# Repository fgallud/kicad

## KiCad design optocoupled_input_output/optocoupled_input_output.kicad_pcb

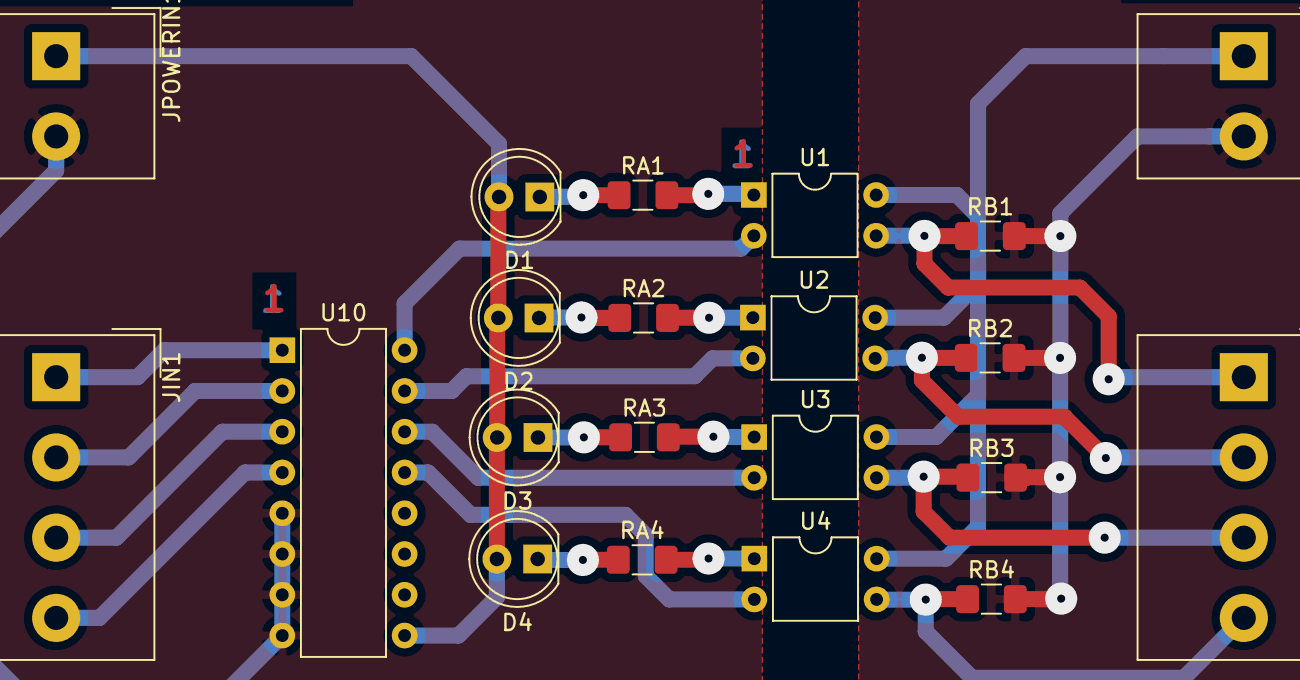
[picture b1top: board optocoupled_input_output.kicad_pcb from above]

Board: 2 copper layers, 21 parts (0 on the bottom side), 24 nets.

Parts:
D1, D2, D3, D4: LED; LED_D5.0mm
JIN1: Conn_01x04; Altech_AK300_1x04_P5.00mm_45-Degree
JOUT1: Conn_01x04; Altech_AK300_1x04_P5.00mm_45-Degree
JPOWERIN1: Conn_01x02; Altech_AK300_1x02_P5.00mm_45-Degree
JPOWEROUT1: Conn_01x02; Altech_AK300_1x02_P5.00mm_45-Degree
RA1, RA2, RA3, RA4: 2K2; R_1206_3216Metric_Pad1.42x1.75mm_HandSolder
RB1, RB2, RB3, RB4: 2K2; R_1206_3216Metric_Pad1.42x1.75mm_HandSolder
U1, U2, U3, U4: PC817; DIP-4_W7.62mm
U10: ULN2003; DIP-16_W7.62mm

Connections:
+3V3: JPOWEROUT1.1, U1.4, U2.4, U3.4, U4.4
+24V: D1.2, D2.2, D3.2, D4.2, JPOWERIN1.1, U10.9
GND: JPOWERIN1.2, U10.5, U10.6, U10.7, U10.8
GNDD: JPOWEROUT1.2, RB1.2, RB2.2, RB3.2, RB4.2
unnamed: D1.1, RA1.1
unnamed: D2.1, RA2.1
unnamed: D3.1, RA3.1
unnamed: D4.1, RA4.1
unnamed: JIN1.1, U10.1
unnamed: JIN1.2, U10.2
unnamed: JIN1.3, U10.3
unnamed: JIN1.4, U10.4
unnamed: JOUT1.1, RB1.1, U1.3
unnamed: JOUT1.2, RB2.1, U2.3
unnamed: JOUT1.3, RB3.1, U3.3
unnamed: JOUT1.4, RB4.1, U4.3
unnamed: RA1.2, U1.1
unnamed: RA2.2, U2.1
unnamed: RA3.2, U3.1
unnamed: RA4.2, U4.1
unnamed: U1.2, U10.16
unnamed: U4.2, U10.13
unnamed: U3.2, U10.14
unnamed: U2.2, U10.15

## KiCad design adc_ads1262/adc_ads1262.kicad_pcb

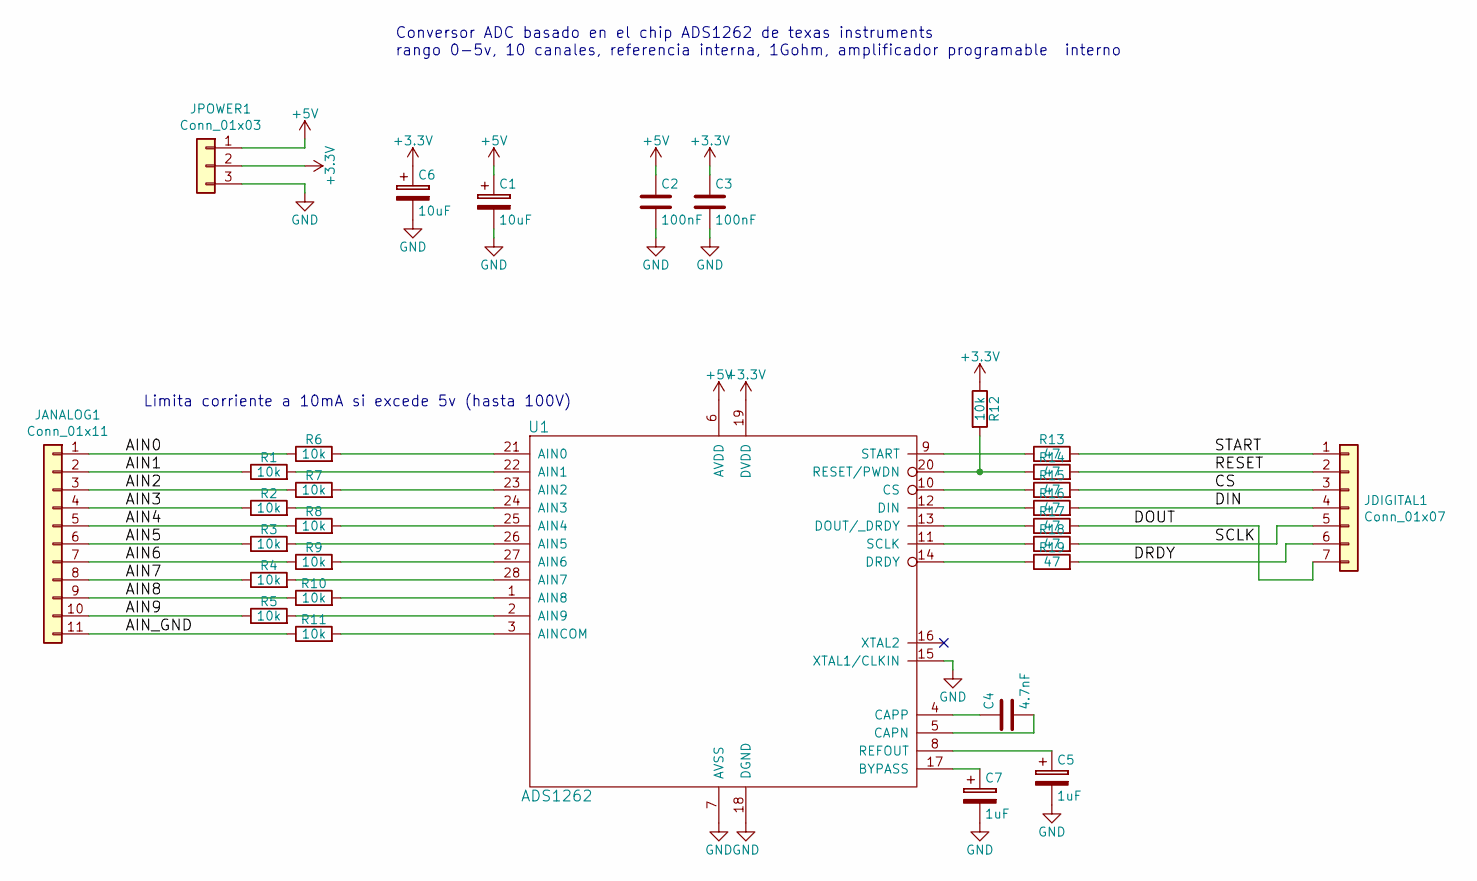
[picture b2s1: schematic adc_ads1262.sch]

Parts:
C1, C6: 10uF; CP_EIA-6032-28_Kemet-C_Pad2.25x2.35mm_HandSolder
C2, C3: 100nF; C_0805_2012Metric_Pad1.15x1.40mm_HandSolder
C4: 4.7nF; C_0805_2012Metric_Pad1.15x1.40mm_HandSolder
C5, C7: 1uF; CP_EIA-6032-28_Kemet-C_Pad2.25x2.35mm_HandSolder
JANALOG1: Conn_01x11; Altech_AK300_1x11_P5.00mm_45-Degree
JDIGITAL1: Conn_01x07; Altech_AK300_1x07_P5.00mm_45-Degree
JPOWER1: Conn_01x03; Altech_AK300_1x03_P5.00mm_45-Degree
R1, R2, R3, R4, R5, R6, R7, R8, R9, R10, R11, R12: 10k; R_0805_2012Metric_Pad1.15x1.40mm_HandSolder
R13, R14, R15, R16, R17, R18, R19: 47; R_0805_2012Metric_Pad1.15x1.40mm_HandSolder
U1: ADS1262; TSSOP-28_4.4x9.7mm_P0.65mm

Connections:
+3V3: C3.1, C6.1, JPOWER1.2, R12.1, U1.19 (DVDD)
+5V: C1.1, C2.1, JPOWER1.1, U1.6 (AVDD)
/AIN0: JANALOG1.1, R6.1
/AIN1: JANALOG1.2, R1.1
/AIN2: JANALOG1.3, R7.1
/AIN3: JANALOG1.4, R2.1
/AIN4: JANALOG1.5, R8.1
/AIN5: JANALOG1.6, R3.1
/AIN6: JANALOG1.7, R9.1
/AIN7: JANALOG1.8, R4.1
/AIN8: JANALOG1.9, R10.1
/AIN9: JANALOG1.10, R5.1
/AIN_GND: JANALOG1.11, R11.1
/CS: JDIGITAL1.3, R15.2
/DIN: JDIGITAL1.4, R16.2
/DOUT: JDIGITAL1.7, R17.2
/DRDY: JDIGITAL1.6, R19.2
/RESET: JDIGITAL1.2, R14.2
/SCLK: JDIGITAL1.5, R18.2
/START: JDIGITAL1.1, R13.2
GND: C1.2, C2.2, C3.2, C5.2, C6.2, C7.2, JPOWER1.3, U1.7 (AVSS), U1.15 (XTAL1/CLKIN), U1.18 (DGND)
unnamed: C4.1, U1.4 (CAPP)
unnamed: C4.2, U1.5 (CAPN)
unnamed: C5.1, U1.8 (REFOUT)
unnamed: C7.1, U1.17 (BYPASS)
unnamed: R1.2, U1.22 (AIN1)
unnamed: R2.2, U1.24 (AIN3)
unnamed: R3.2, U1.26 (AIN5)
unnamed: R4.2, U1.28 (AIN7)
unnamed: R5.2, U1.2 (AIN9)
unnamed: R6.2, U1.21 (AIN0)
unnamed: R7.2, U1.23 (AIN2)
unnamed: R8.2, U1.25 (AIN4)
unnamed: R9.2, U1.27 (AIN6)
unnamed: R10.2, U1.1 (AIN8)
unnamed: R11.2, U1.3 (AINCOM)
unnamed: R12.2, R14.1, U1.20 (RESET/PWDN)
unnamed: R13.1, U1.9 (START)
unnamed: R15.1, U1.10 (CS)
unnamed: R16.1, U1.12 (DIN)
unnamed: R17.1, U1.13 (DOUT/_DRDY)
unnamed: R18.1, U1.11 (SCLK)
unnamed: R19.1, U1.14 (DRDY)

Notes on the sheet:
Conversor ADC basado en el chip ADS1262 de texas instruments rango 0-5v, 10 canales, referencia interna, 1Gohm, amplificador programable interno
Limita corriente a 10mA si excede 5v (hasta 100V)

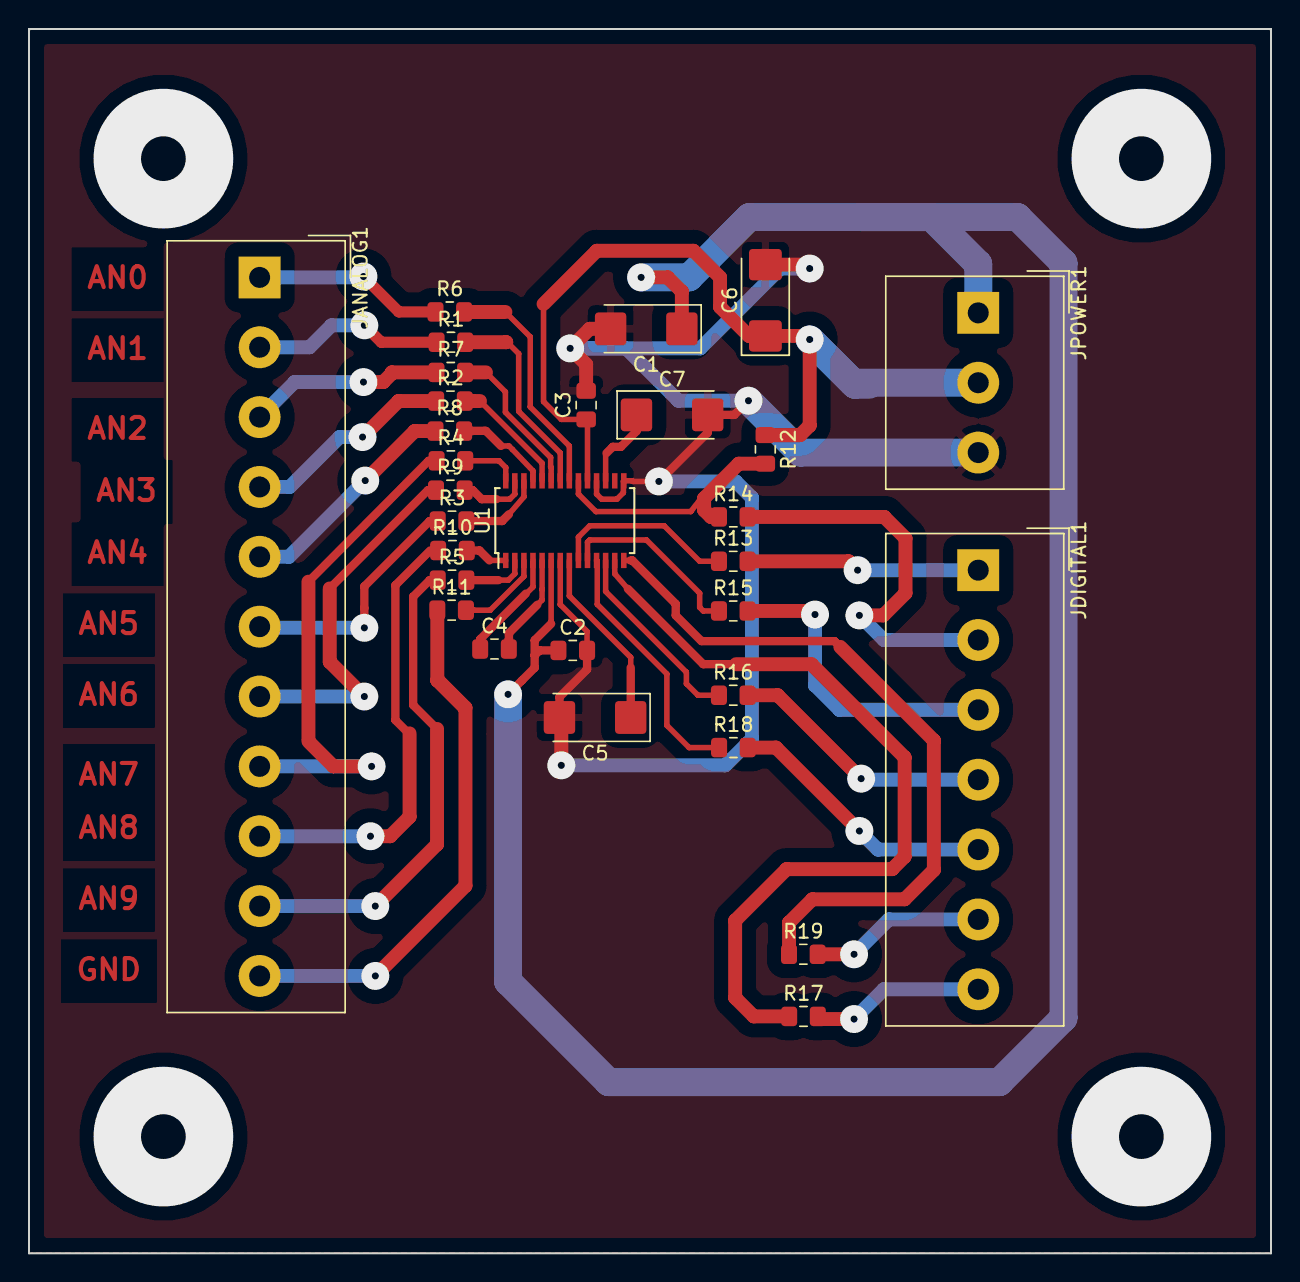
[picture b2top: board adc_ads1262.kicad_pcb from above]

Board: 2 copper layers, 88.9 x 87.6 mm, 30 parts (0 on the bottom side), 43 nets.

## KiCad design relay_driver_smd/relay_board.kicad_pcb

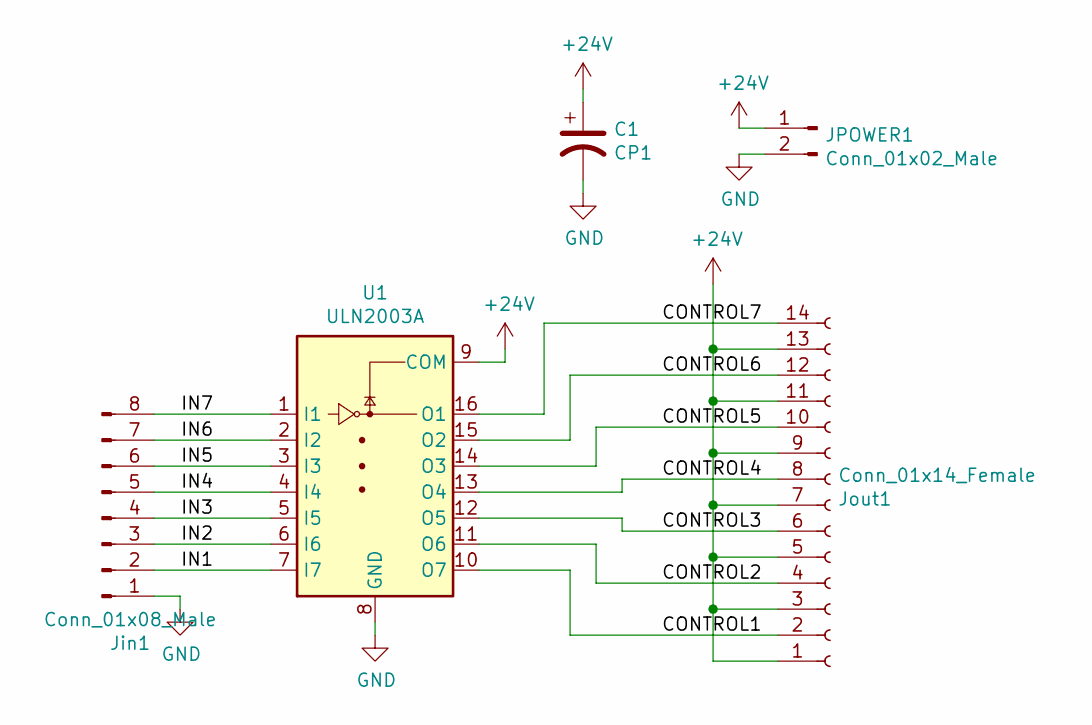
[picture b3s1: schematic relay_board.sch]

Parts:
C1: CP1; CP_EIA-7361-438_AVX-U_Pad2.18x3.30mm_HandSolder
JPOWER1: Conn_01x02_Male; Altech_AK300_1x02_P5.00mm_45-Degree
Jin1: Conn_01x08_Male; Altech_AK300_1x08_P5.00mm_45-Degree
Jout1: Conn_01x14_Female; Altech_AK300_1x14_P5.00mm_45-Degree
U1: ULN2003A; SOIC-16_4.55x10.3mm_P1.27mm

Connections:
+24V: C1.1, JPOWER1.1, Jout1.1, Jout1.3, Jout1.5, Jout1.7, Jout1.9, Jout1.11, Jout1.13, U1.9 (COM)
/CONTROL1: Jout1.2, U1.10 (O7)
/CONTROL2: Jout1.4, U1.11 (O6)
/CONTROL3: Jout1.6, U1.12 (O5)
/CONTROL4: Jout1.8, U1.13 (O4)
/CONTROL5: Jout1.10, U1.14 (O3)
/CONTROL6: Jout1.12, U1.15 (O2)
/CONTROL7: Jout1.14, U1.16 (O1)
/IN1: Jin1.2, U1.7 (I7)
/IN2: Jin1.3, U1.6 (I6)
/IN3: Jin1.4, U1.5 (I5)
/IN4: Jin1.5, U1.4 (I4)
/IN5: Jin1.6, U1.3 (I3)
/IN6: Jin1.7, U1.2 (I2)
/IN7: Jin1.8, U1.1 (I1)
GND: C1.2, JPOWER1.2, Jin1.1, U1.8 (GND)

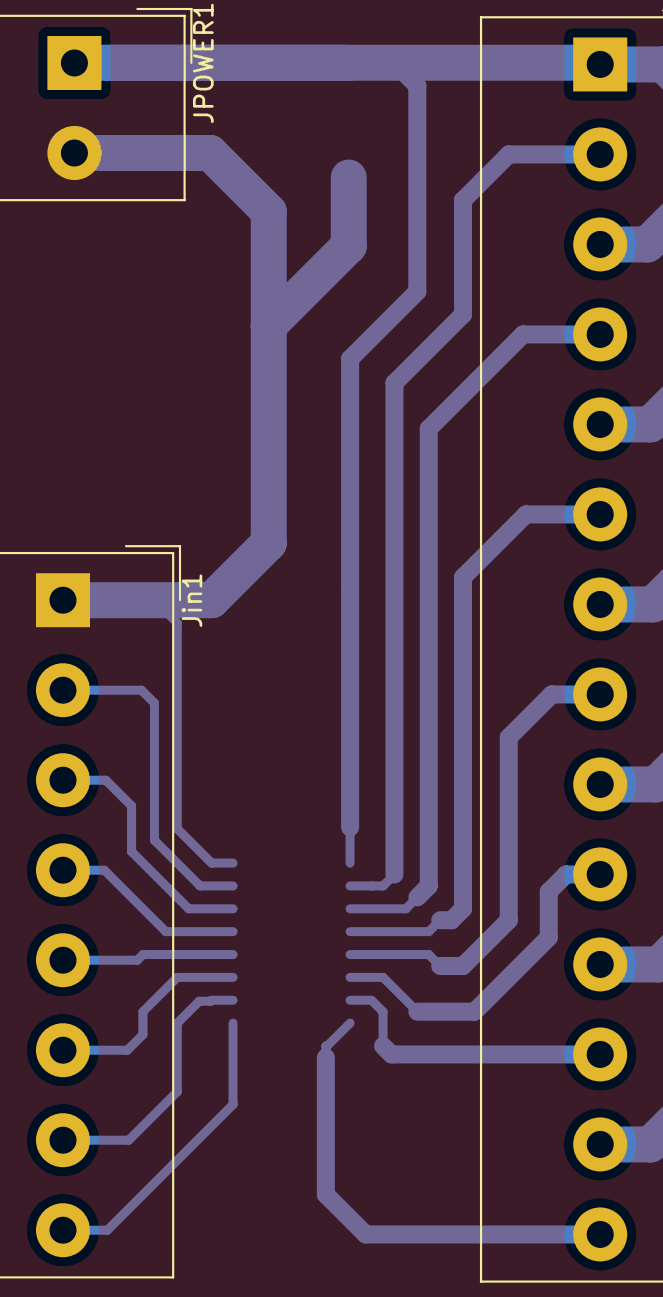
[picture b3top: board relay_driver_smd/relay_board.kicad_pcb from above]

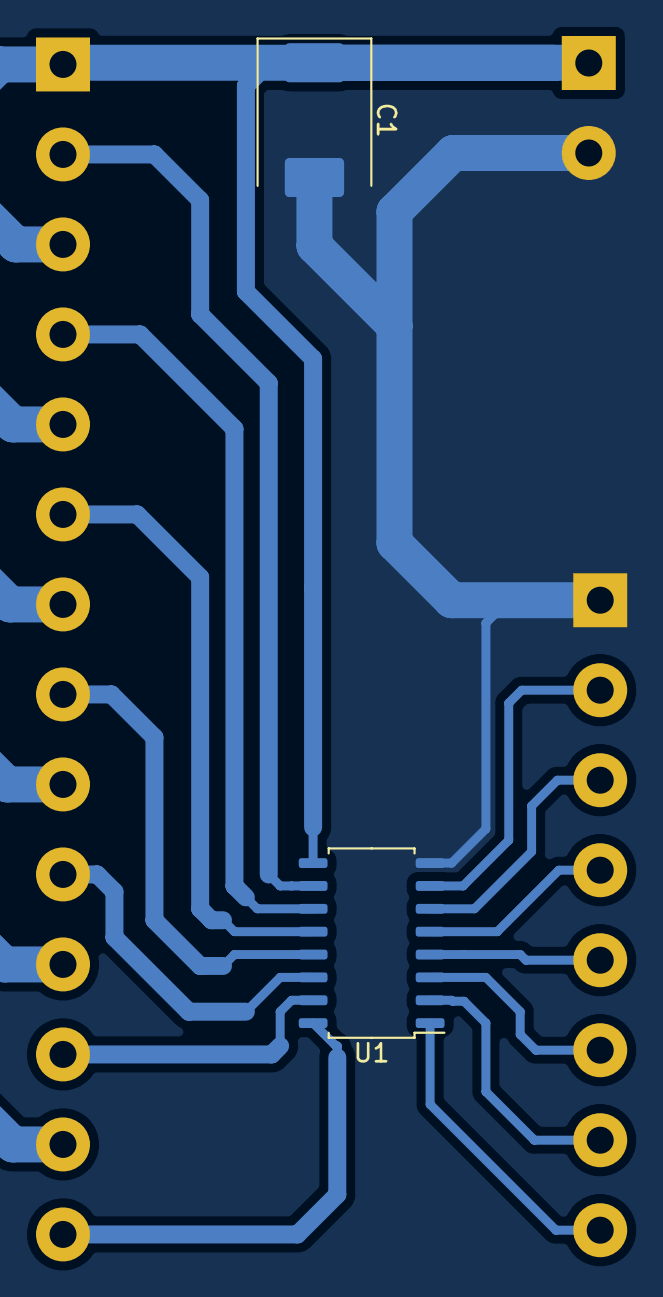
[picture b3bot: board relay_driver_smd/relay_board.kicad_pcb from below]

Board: 2 copper layers, 5 parts (2 on the bottom side), 16 nets.

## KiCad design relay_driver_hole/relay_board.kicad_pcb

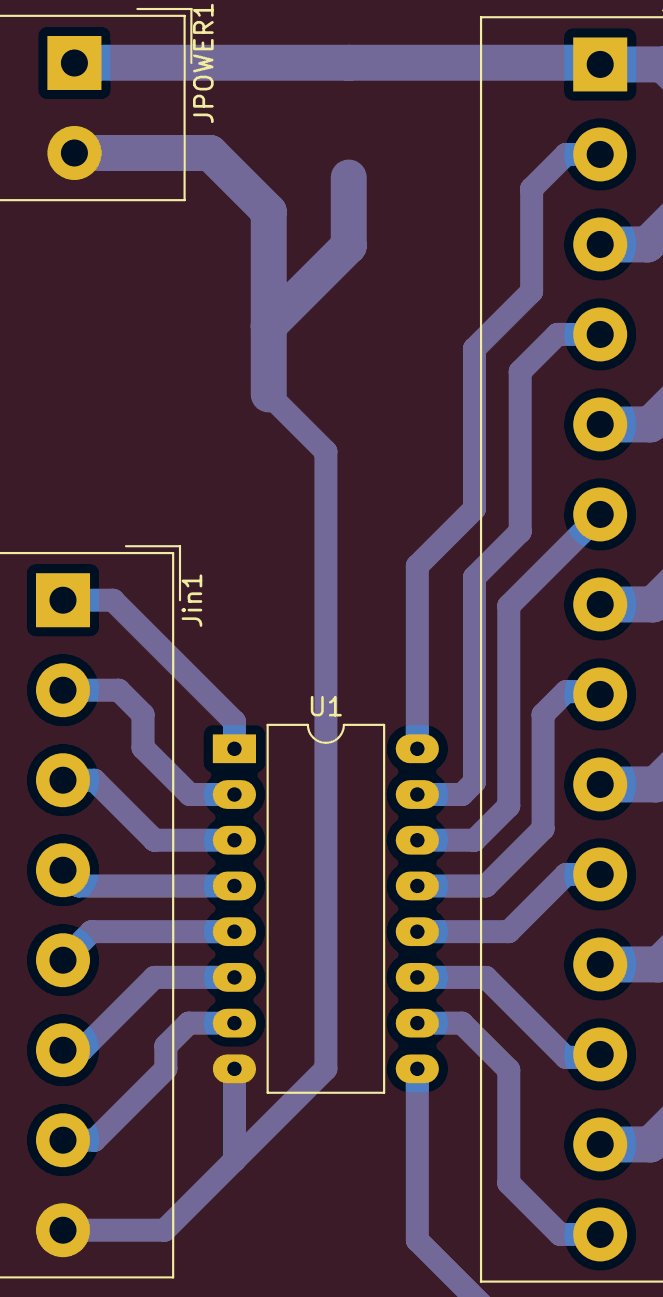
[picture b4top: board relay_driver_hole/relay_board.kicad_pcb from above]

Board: 2 copper layers, 5 parts (1 on the bottom side), 16 nets.

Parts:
C1: CP1; CP_EIA-7361-438_AVX-U_Pad2.18x3.30mm_HandSolder
JPOWER1: Conn_01x02_Male; Altech_AK300_1x02_P5.00mm_45-Degree
Jin1: Conn_01x08_Male; Altech_AK300_1x08_P5.00mm_45-Degree
Jout1: Conn_01x14_Female; Altech_AK300_1x14_P5.00mm_45-Degree
U1: ULN2003A; DIP-16_W10.16mm_LongPads

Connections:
+24V: C1.1, JPOWER1.1, Jout1.1, Jout1.3, Jout1.5, Jout1.7, Jout1.9, Jout1.11, Jout1.13, U1.9
/CONTROL1: Jout1.2, U1.16
/CONTROL2: Jout1.4, U1.15
/CONTROL3: Jout1.6, U1.14
/CONTROL4: Jout1.8, U1.13
/CONTROL5: Jout1.10, U1.12
/CONTROL6: Jout1.12, U1.11
/CONTROL7: Jout1.14, U1.10
/IN1: Jin1.1, U1.1
/IN2: Jin1.2, U1.2
/IN3: Jin1.3, U1.3
/IN4: Jin1.4, U1.4
/IN5: Jin1.5, U1.5
/IN6: Jin1.6, U1.6
/IN7: Jin1.7, U1.7
GND: C1.2, JPOWER1.2, Jin1.8, U1.8
